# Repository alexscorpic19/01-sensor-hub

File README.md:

# 🏭 **Industrial IoT Sensor Hub (v1.1)**

### **High-Performance Data Acquisition System with ESP32-S3 & FreeRTOS**

Este proyecto demuestra una solución IoT **End-to-End**, conectando
hardware embebido (C++) con visualización web moderna (React).

------------------------------------------------------------------------

## 🖥️ **Real-Time Dashboard Interface**

-   **Communication:** Conexión directa a HiveMQ Cloud vía **Secure
    WebSockets (WSS)**\
-   **Latency:** Actualizaciones en tiempo real (\<100ms) desde el
    ESP32-S3\
-   **Data Visualization:** Lectura sincronizada de sensores ambientales
    (BME280) e inerciales (MPU6050)\
-   **Protocol:** Decodificación de JSON directamente en navegador

------------------------------------------------------------------------

## 📦 **Hardware Revision v1.1 --- Carrier Board**

La placa contiene un diseño modular que integra ESP32-S3, sensores,
etapa de potencia y puertos de expansión.

### ⚡ Schematic & PCB Layout

<table>
  <tr>
    <td align="center"><strong>3D Render (Physical)</strong></td>
    <td align="center"><strong>Schematic (Logical)</strong></td>
  </tr>
  <tr>
    <td align="center">
      
    </td>
    <td align="center">
      
    </td>
  </tr>
  <tr>
    <td align="center"><em>Designed in KiCad 9 — Raytracing Render</em></td>
    <td align="center"><em>Low-Side Switch & I²C Bus Topology</em></td>
  </tr>
</table>

### 🔩 **Technical Specs**

  -----------------------------------------------------------------------
  Subsystem             Components              Description
  --------------------- ----------------------- -------------------------
  **MCU Core**          ESP32-S3-DevKitC-1      Dual-core Xtensa LX7 @
                                                240MHz, WiFi + BLE 5.0

  **Inertial**          MPU6050                 6-Axis Accelerometer &
                                                Gyroscope (I2C: 0x68)

  **Environmental**     BME280                  Temp, Humidity, Pressure
                                                (I2C: 0x77)

  **Actuator Control**  2N2222 + Flyback Diode  Low-Side Switch para
                                                relés/motores (GPIO 11)

  **Audio Input**       Header for INMP441      Puerto I2S para micrófono
                                                MEMS

  **Expansion**         8-Pin Header            GPIOs adicionales +
                                                rieles 5V/3.3V
  -----------------------------------------------------------------------

### 📂 **Manufacturing Files**

Archivos Gerber listos para producción:

➡️ **[Download Gerbers v1.1
(ZIP)](hardware/sensor-hub-carrier/Gerbers/Gerbers_SensorHub_v1.1.zip)**

------------------------------------------------------------------------

## 📂 **Project Structure (ESP-IDF Standard)**

``` text
01-sensor-hub/
├── components/        # Modular Drivers (C++ Classes)
│   ├── bme280/        # I2C Driver for Environmental Sensor
│   ├── mpu6050/       # I2C Driver for IMU
│   └── wifi_connect/  # WiFi Station Manager
├── main/              # Application Entry Point (FreeRTOS Tasks)
├── sensor-dashboard/  # React Frontend (Vite + MQTT.js)
├── hardware/          # KiCad 9 Design Files (Schematic, PCB, Gerbers)
├── tools/             # Python Scripts for data ingestion testing
└── docs/              # Documentation & assets
```

------------------------------------------------------------------------

# 🔧 **Setup Instructions**

------------------------------------------------------------------------

## 1️⃣ **Firmware Deployment (ESP32-S3)**

**Prerequisite:** VS Code + Espressif IDF Extension (v5.x)

1.  Abre el proyecto en VS Code\
2.  Configura WiFi en:\
    `components/wifi_connect/include/wifi_connect.h`\
3.  Configura credenciales MQTT en:\
    `main/main.cpp`\
4.  Compila usando el icono **Build (Cylinder)**\
5.  Flashea el firmware con **Flash (Lightning)**

------------------------------------------------------------------------

## 2️⃣ **Dashboard Setup (React)**

1.  Entra al directorio:

    ``` bash
    cd sensor-dashboard
    ```

2.  Instala dependencias:

    ``` bash
    npm install
    ```

3.  Ejecuta el servidor de desarrollo:

    ``` bash
    npm run dev
    ```

4.  Abre en el navegador:\
    **http://localhost:5173**

------------------------------------------------------------------------

## 3️⃣ **HiveMQ Cloud Configuration**

1.  Crea un cluster gratuito en HiveMQ Cloud\
2.  Genera credenciales (User/Password)\
3.  Actualiza los archivos:
    -   Frontend: `App.jsx`\
    -   Firmware: `main.cpp`

------------------------------------------------------------------------

# 📊 **Data Flow Architecture**

1.  **Sensor Acquisition:** BME280 & MPU6050 → Bus I²C\
2.  **Edge Processing:** ESP32-S3 serializa lecturas en JSON (cJSON)\
3.  **Cloud Routing:** Publicación segura vía MQTT (TLS 1.2) a HiveMQ
    Cloud\
4.  **Real-Time Display:** React + MQTT.js → WebSockets (WSS)

------------------------------------------------------------------------

# 📜 **License**

**MIT License --- Open Source**

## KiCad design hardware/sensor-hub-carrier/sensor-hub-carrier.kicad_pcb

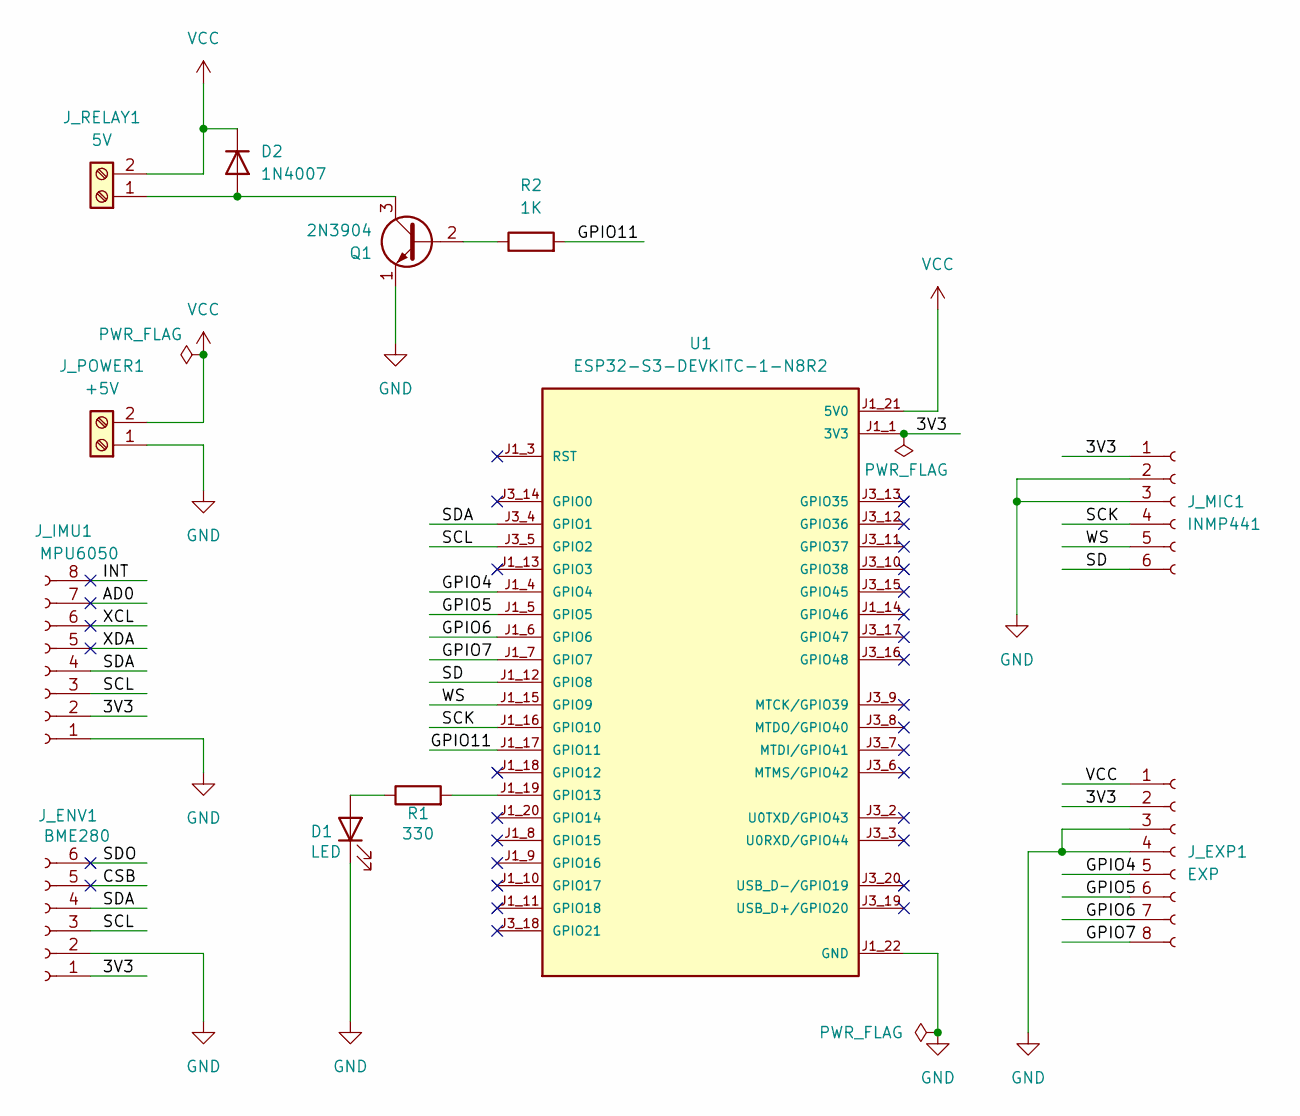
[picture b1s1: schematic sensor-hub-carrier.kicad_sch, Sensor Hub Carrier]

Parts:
D1: LED; LED_D3.0mm
D2: 1N4007; D_DO-41_SOD81_P10.16mm_Horizontal
J_ENV1: BME280; PinSocket_1x06_P2.54mm_Vertical
J_EXP1: EXP; PinSocket_1x08_P2.54mm_Vertical
J_IMU1: MPU6050; PinSocket_1x08_P2.54mm_Vertical
J_MIC1: INMP441; PinSocket_1x06_P2.54mm_Vertical
J_POWER1: +5V; TerminalBlock_bornier-2_P5.08mm
J_RELAY1: 5V; TerminalBlock_bornier-2_P5.08mm
Q1: 2N3904; TO-92_Inline
R1: 330; R_Axial_DIN0207_L6.3mm_D2.5mm_P10.16mm_Horizontal
R2: 1K; R_Axial_DIN0207_L6.3mm_D2.5mm_P10.16mm_Horizontal
U1: ESP32-S3-DEVKITC-1-N8R2; XCVR_ESP32-S3-DEVKITC-1-N8R2; PARTREV V1

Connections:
3V3: J_ENV1.1, J_EXP1.2, J_IMU1.2, J_MIC1.1, U1.J1_1 (3V3), U1.J1_2 (3V3)
/AD0: J_IMU1.7
/CSB: J_ENV1.5
/GPIO4: J_EXP1.5, U1.J1_4 (GPIO4)
/GPIO5: J_EXP1.6, U1.J1_5 (GPIO5)
/GPIO6: J_EXP1.7, U1.J1_6 (GPIO6)
/GPIO7: J_EXP1.8, U1.J1_7 (GPIO7)
/GPIO11: R2.2, U1.J1_17 (GPIO11)
/INT: J_IMU1.8
/SCK: J_MIC1.4, U1.J1_16 (GPIO10)
/SCL: J_ENV1.3, J_IMU1.3, U1.J3_5 (GPIO2)
/SD: J_MIC1.6, U1.J1_12 (GPIO8)
/SDA: J_ENV1.4, J_IMU1.4, U1.J3_4 (GPIO1)
/SDO: J_ENV1.6
/WS: J_MIC1.5, U1.J1_15 (GPIO9)
/XCL: J_IMU1.6
/XDA: J_IMU1.5
GND: D1.1 (K), J_ENV1.2, J_EXP1.3, J_EXP1.4, J_IMU1.1, J_MIC1.2, J_MIC1.3, J_POWER1.1, Q1.1 (E), U1.J1_22 (GND), U1.J3_1 (GND), U1.J3_21 (GND), U1.J3_22 (GND)
unnamed: D1.2 (A), R1.1
unnamed: D2.2 (A), J_RELAY1.1, Q1.3 (C)
unnamed: Q1.2 (B), R2.1
unnamed: R1.2, U1.J1_19 (GPIO13)
VCC: D2.1 (K), J_EXP1.1, J_POWER1.2, J_RELAY1.2, U1.J1_21 (5V0)

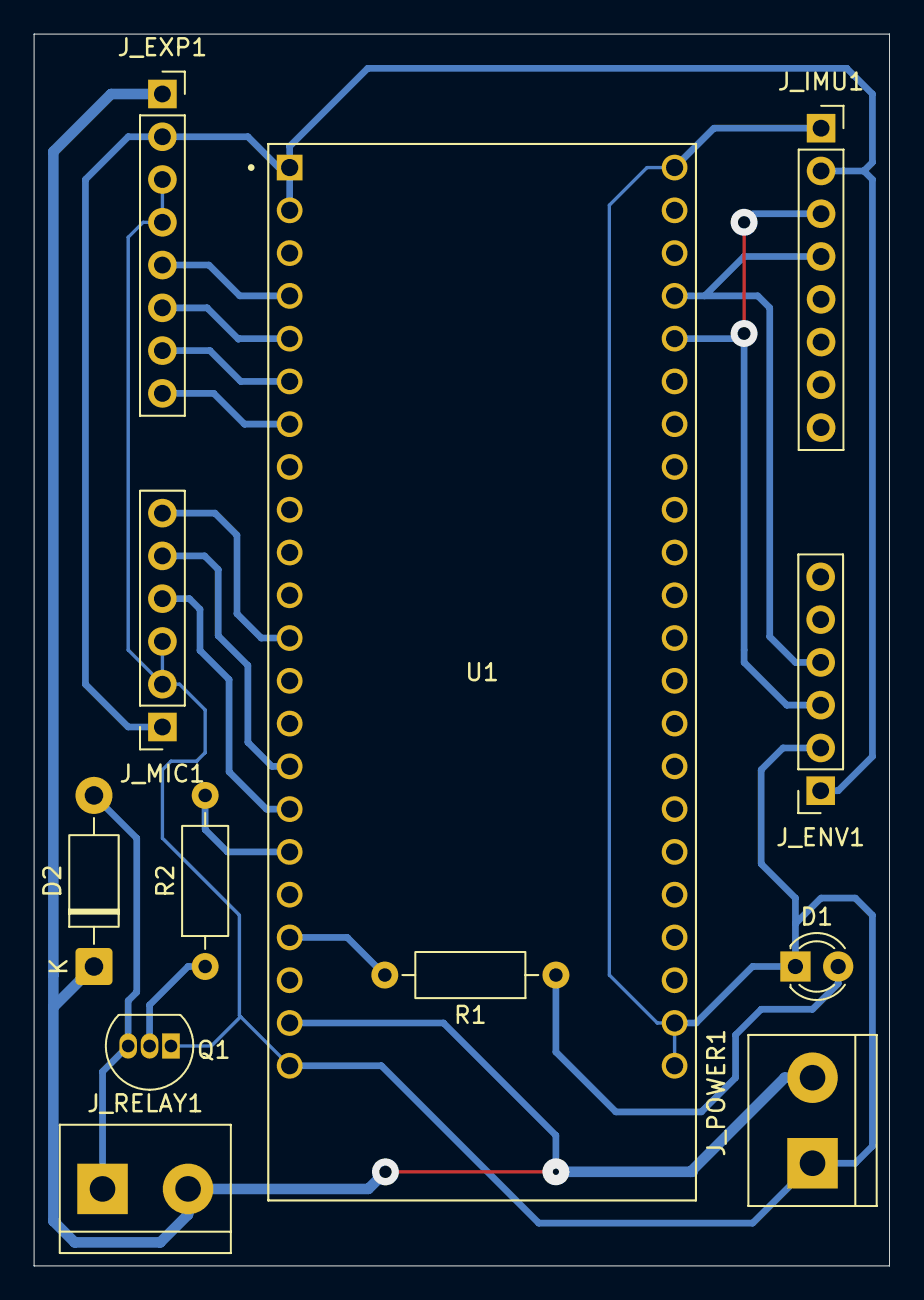
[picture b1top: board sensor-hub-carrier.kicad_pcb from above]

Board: 2 copper layers, 50.8 x 73.2 mm, 12 parts (0 on the bottom side), 17 nets.

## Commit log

2025-11-24 feat: Initial ESP32-S3 setup with Wokwi simulation
2025-11-25 feat: Add BME280 C++ driver structure (Mock)
2025-11-25 feat: Implement Multi-Sensor Architecture with MPU6050 (I2C Shared Bus)
2025-11-27 feat: Full IoT Pipeline working! ESP32 to HiveMQ Cloud via MQTT TLS
2025-11-28 feat: Implement full sensor fusion JSON payload with MPU6050 and BME280
2025-11-28 feat: Add React Dashboard frontend
2025-11-28 docs: Polish README with project structure
2025-11-29 feat: Add final PCB design with custom libraries and 3D render
2025-11-30 docs: Release Hardware v1.1 (Relay Driver + Expansion Ports)
2025-11-30 add Gerbers folder
2025-11-30 modified: README.MD name folder Gerbers
2025-11-30 modified: README.MD route Gerbers
2025-12-01 fix: Correct relative path to Gerbers ZIP
